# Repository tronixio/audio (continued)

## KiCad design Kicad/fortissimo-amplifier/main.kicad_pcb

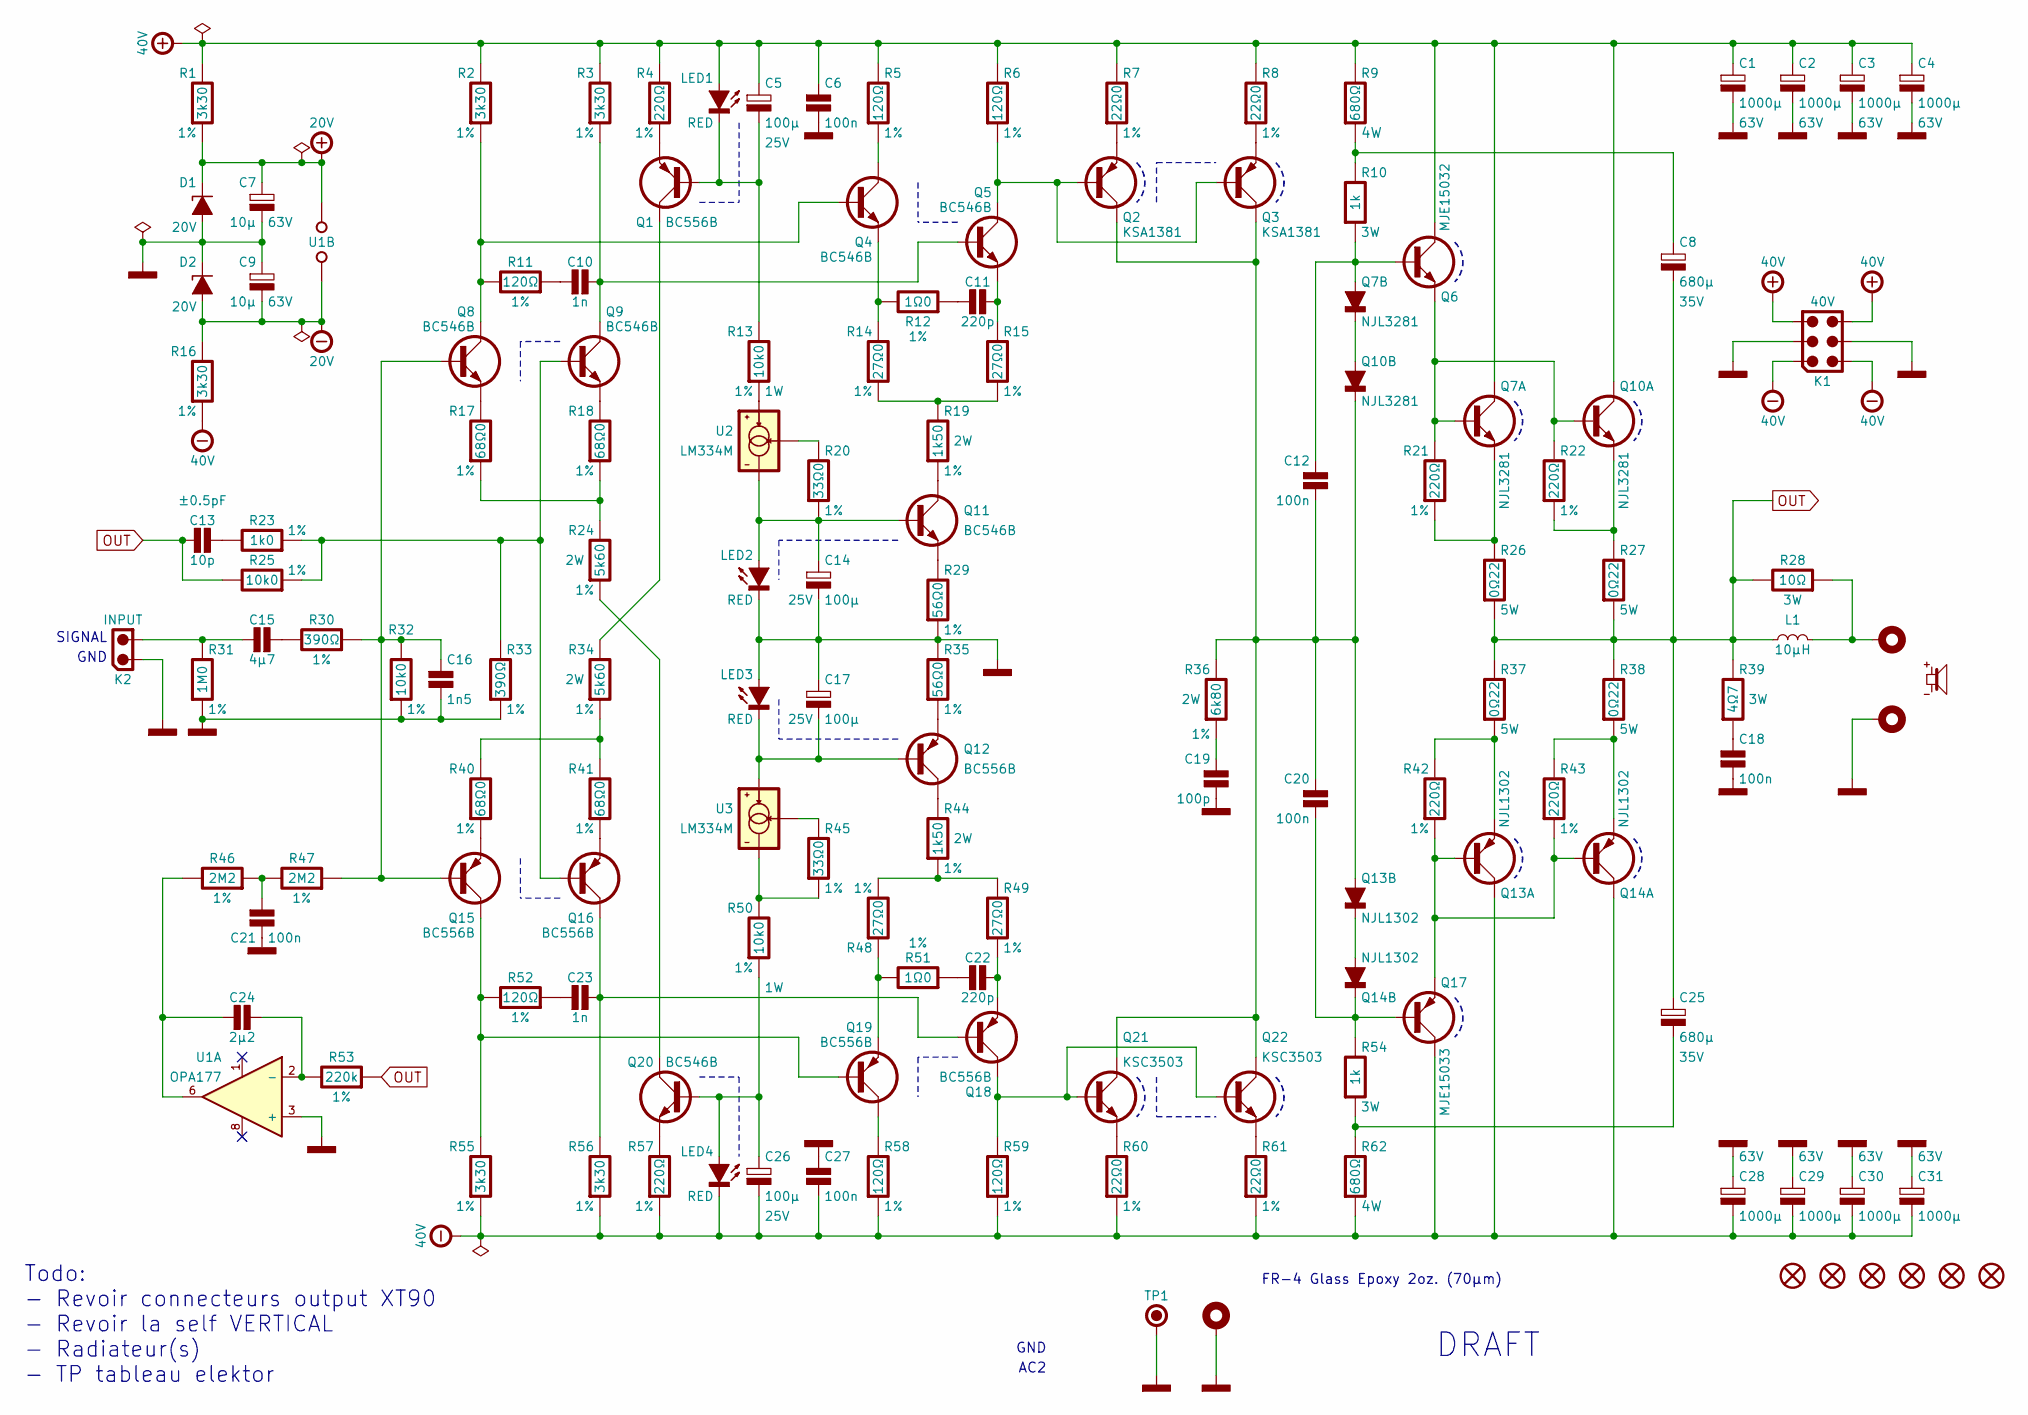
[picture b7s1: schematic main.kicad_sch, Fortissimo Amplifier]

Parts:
C1, C2, C3, C4, C28, C29, C30, C31: 1000µ; CAPACITOR-ELECTROLYTIC-RADIAL-160-350-075-WURTH; Voltage 63V; Tolerance 20%; Mouser 710-860040780017
C5, C14, C17, C26: 100µ; CAPACITOR-ELECTROLYTIC-RADIAL-080-115-035-WURTH; Tolerance 20%; Voltage 25V; Mouser 710-860240474005
C6, C12, C20, C21, C27: 100n; WIMA-FILM-CAPACITOR-RADIAL-100-025-070-075; Tolerance 5%; Voltage 100V; Mouser 505-MKS4D031002AJSSD
C7, C9: 10µ; CAPACITOR-ELECTROLYTIC-RADIAL-050-110-020-WURTH; Voltage 63V; Tolerance 20%; Mouser 710-860020772010
C8, C25: 680µ; CAPACITOR-ELECTROLYTIC-RADIAL-130-200-050-WURTH; Voltage 35V; Tolerance 20%; Mouser 710-860080578019
C10, C23: 1n; WIMA-FILM-CAPACITOR-RADIAL-072-025-065-050; Voltage 63V; Tolerance 5%; Mouser 505-FKS2C01101A0JN0
C11, C22: 220p; WIMA-FILM-CAPACITOR-RADIAL-072-045-060-050; Tolerance 2.5%; Voltage 100V; Mouser 505-FKP2220/100/2.5
C13: 10p; CAPACITOR-SMD-1206; Voltage 100V; Tolerance ±0.5pF; Mouser 581-12061A100DAT2A
C15: 4µ7; WIMA-FILM-CAPACITOR-RADIAL-072-085-140-050; Tolerance 5%; Voltage 63V; Mouser 505-MKS24.7/63/5
C16: 1n5; WIMA-FILM-CAPACITOR-RADIAL-072-025-065-050; Voltage 100V; Tolerance 5%; Mouser 505-FKS2D011501A0JA0
C18: 100n; KEMET-R79-100-050-100-050; Tolerance 5%; Voltage 160V; Mouser 80-R79GC3100Z340J
C19: 100p; WIMA-FILM-CAPACITOR-RADIAL-072-045-060-050; Voltage 100V; Tolerance 2.5%; Mouser 505-FKP2100/100/2.5
C24: 2µ2; WIMA-FILM-CAPACITOR-RADIAL-072-072-130-050; Tolerance 5%; Voltage 63V; Mouser 505-MKS22.2/63/5
D1, D2: 20V; SOD-123; Mouser 771-BZT52-C20
H1, H2, H9: MOUNTING-HOLE-3MM-PAD-VIA
H3, H4, H5, H6, H7, H8: MOUNTING-HOLE-3MM-MASK
K1: 40V; MOLEX-39288060; Mouser 538-39-28-8060
K2: INPUT; MOLEX-532530270; Mouser 538-53253-0270
L1: 10µH; WURTH-744710615
LED1, LED2, LED3, LED4: RED; LED-TH-RECTANGULAR-5MM-2MM; Mouser 630-HLMP-S201
Q1, Q12, Q15, Q16, Q18, Q19: BC556B; TO-92-INLINE-WIDE; Mouser 512-BC556BTF
Q2, Q3: KSA1381; TO-126-3-VERTICAL; Mouser 512-KSA1381ESTU
Q4, Q5, Q8, Q9, Q11, Q20: BC546B; TO-92-INLINE-WIDE; Mouser 512-BC546BTF
Q6: MJE15032; TO-220-3-VERTICAL; Mouser 863-MJE15032G
Q7, Q10: NJL3281; TO-264-5-VERTICAL; Mouser 863-NJL3281DG
Q13, Q14: NJL1302; TO-264-5-VERTICAL; Mouser 863-NJL1302DG
Q17: MJE15033; TO-220-3-VERTICAL; Mouser 863-MJE15033G
Q21, Q22: KSC3503; TO-126-3-VERTICAL; Mouser 512-KSC3503DS
R1, R2, R3, R16, R55, R56: 3k30; RESISTOR-SMD-2512; Tolerance 1%; Mouser 603-RC2512FK-073K3L
R4, R21, R22, R42, R43, R57: 220Ω; RESISTOR-SMD-2512; Tolerance 1%; Mouser 603-RC2512FK-07220RL
R5, R6, R11, R52, R58, R59: 120Ω; RESISTOR-SMD-2512; Tolerance 1%; Mouser 603-RC2512FK-07120RL
R7, R8, R60, R61: 22Ω0; RESISTOR-SMD-2512; Tolerance 1%; Mouser 603-RC2512FK-0722RL
R9, R62: 680Ω; RESISTOR-SMD-2816; Tolerance 5%; Mouser 279-3540680RJT
R10, R54: 1k; RESISTOR-SMD-2512-POWER; Tolerance 5%; Mouser 279-35221K0JT
R12, R51: 1Ω0; RESISTOR-SMD-2512; Tolerance 1%; Mouser 603-RC2512FK-071RL
R13, R25, R32, R50: 10k0; RESISTOR-SMD-2512; Tolerance 1%; Mouser 603-RC2512FK-0710KL
R14, R15, R48, R49: 27Ω0; RESISTOR-SMD-2512; Tolerance 1%; Mouser 603-RC2512FK-0727RL
R17, R18, R40, R41: 68Ω0; RESISTOR-SMD-2512; Tolerance 1%; Mouser 603-RC2512FK-0768RL
R19, R44: 1k50; RESISTOR-SMD-2512-POWER; Tolerance 1%; Mouser 279-CRGP2512F1K5
R20, R45: 33Ω0; RESISTOR-SMD-2512; Tolerance 1%; Mouser 603-RC2512FK-0733RL
R23: 1k0; RESISTOR-SMD-2512; Tolerance 1%; Mouser 603-RC2512FK-071KL
R24, R34: 5k60; RESISTOR-SMD-2512-POWER; Tolerance 1%; Mouser 279-CRGP2512F5K6
R26, R27, R37, R38: 0Ω22; KOA-SPEER-BPR58; Tolerance 5%; Mouser 660-BPR58CR22J
R28: 10Ω; RESISTOR-SMD-2512-POWER; Tolerance 5%; Mouser 279-352210RJT
R29, R35: 56Ω0; RESISTOR-SMD-2512; Tolerance 1%; Mouser 603-RC2512FK-0756RL
R30, R33: 390Ω; RESISTOR-SMD-2512; Tolerance 1%; Mouser 603-RC2512FK-07390RL
R31: 1M0; RESISTOR-SMD-2512; Tolerance 1%; Mouser 603-RC2512FK-071ML
R36: 6k80; RESISTOR-SMD-2512; Tolerance 1%; Mouser 279-CRGP2512F6K8
R39: 4Ω7; RESISTOR-SMD-2512-POWER; Tolerance 5%; Mouser 279-35224R7JT
R46, R47: 2M2; RESISTOR-SMD-2512; Tolerance 1%; Mouser 603-RC2512FK-072M2L
R53: 220k; RESISTOR-SMD-2512; Tolerance 1%; Mouser 603-RC2512FK-07220KL
TP1: KEYSTONE-5006; Mouser 534-5006
U1: OPA177; SOIC-08; Mouser 595-OPA177GS/2K5
U2, U3: LM334M; SOIC-08; Mouser 926-LM334MX/NOPB
X1: (no value)

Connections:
+20V: C7.1, D1.1 (C), R1.2, U1.7 (V+)
+40V: C1.1, C2.1, C3.1, C4.1, C5.1, C6.1, K1.3, K1.6, LED1.2 (A), Q6.2 (C), Q7.3 (C), Q10.3 (C), R1.1, R2.1, R3.1, R4.1, R5.1, R6.1, R7.1, R8.1, R9.1
-20V: C9.2, D2.2 (A), R16.1, U1.4 (V-)
-40V: C26.2, C27.2, C28.2, C29.2, C30.2, C31.2, K1.1, K1.4, LED4.1 (C), Q13.3 (C), Q14.3 (C), Q17.2 (C), R16.2, R55.2, R56.2, R57.2, R58.2, R59.2, R60.2, R61.2, R62.2
GND: C1.2, C2.2, C3.2, C4.2, C6.2, C7.2, C9.1, C14.2, C16.2, C17.1, C18.2, C19.2, C21.2, C27.1, C28.1, C29.1, C30.1, C31.1, D1.2 (A), D2.1 (C), H2.1, H9.1, K1.2, K1.5, K2.1, LED2.1 (C), LED3.2 (A), R29.2, R31.2, R32.2, R33.2, R35.1, TP1.1, U1.3 (+)
unnamed: C8.1, R9.2, R10.1
unnamed: C10.1, R11.2
unnamed: C11.1, R12.2
unnamed: C13.2, R23.1
unnamed: C15.1, K2.2, R31.1
unnamed: C15.2, R30.1
unnamed: C18.1, R39.2
unnamed: C19.1, R36.2
unnamed: C21.1, R46.2, R47.1
unnamed: C22.1, R51.2
unnamed: C23.1, R52.2
unnamed: C24.1, R46.1, U1.6
unnamed: C25.2, R54.2, R62.1
unnamed: H1.1, L1.2, R28.2
unnamed: C5.2, LED1.1 (C), Q1.2 (B), R13.1
unnamed: C14.1, LED2.2 (A), Q11.2 (B), R20.2, U2.2 (V-), U2.3 (V-), U2.6 (V-), U2.7 (V-)
unnamed: C17.2, LED3.1 (C), Q12.2 (B), U3.4 (V+)
unnamed: C26.1, LED4.2 (A), Q20.2 (B), R50.2
unnamed: Q1.1 (C), R34.1
unnamed: Q1.3 (E), R4.2
unnamed: Q2.3 (B), Q3.3 (B), Q5.1 (C), R6.2
unnamed: Q2.1 (E), R7.2
unnamed: Q3.1 (E), R8.2
unnamed: Q4.2 (B), Q8.1 (C), R2.2, R11.1
unnamed: Q4.1 (C), R5.2
unnamed: Q4.3 (E), R12.1, R14.1
unnamed: C10.2, Q5.2 (B), Q9.1 (C), R3.2
unnamed: C11.2, Q5.3 (E), R15.1
unnamed: C12.1, Q6.1 (B), Q7.4 (A), R10.2
unnamed: Q7.2 (E), R21.2, R26.1
unnamed: Q8.3 (E), R17.1
unnamed: Q9.3 (E), R18.1
unnamed: Q6.3 (E), Q7.1 (B), Q10.1 (B), R21.1, R22.1
unnamed: Q10.2 (E), R22.2, R27.1
unnamed: Q7.5 (K), Q10.4 (A)
unnamed: C12.2, C20.1, Q2.2 (C), Q3.2 (C), Q10.5 (K), Q13.4 (A), Q21.2 (C), Q22.2 (C), R36.1
unnamed: Q11.1 (C), R19.2
unnamed: Q11.3 (E), R29.1
unnamed: Q12.1 (C), R44.1
unnamed: Q12.3 (E), R35.2
unnamed: Q13.1 (B), Q14.1 (B), Q17.3 (E), R42.2, R43.2
unnamed: Q13.2 (E), R37.2, R42.1
unnamed: Q13.5 (K), Q14.4 (A)
unnamed: Q14.2 (E), R38.2, R43.1
unnamed: C20.2, Q14.5 (K), Q17.1 (B), R54.1
unnamed: C16.1, Q8.2 (B), Q15.2 (B), R30.2, R32.1, R47.2
unnamed: Q15.1 (C), Q19.2 (B), R52.1, R55.1
unnamed: Q15.3 (E), R40.2
unnamed: Q9.2 (B), Q16.2 (B), R23.2, R25.2, R33.1
unnamed: C23.2, Q16.1 (C), Q18.2 (B), R56.1
unnamed: Q16.3 (E), R41.2
unnamed: Q18.1 (C), Q21.3 (B), Q22.3 (B), R59.1
unnamed: C22.2, Q18.3 (E), R49.2
unnamed: Q19.1 (C), R58.1
unnamed: Q19.3 (E), R48.2, R51.1
unnamed: Q20.1 (C), R24.2
unnamed: Q20.3 (E), R57.1
unnamed: Q21.1 (E), R60.1
unnamed: Q22.1 (E), R61.1
unnamed: R14.2, R15.2, R19.1
unnamed: R17.2, R18.2, R24.1
unnamed: R34.2, R40.1, R41.1
unnamed: R44.2, R48.1, R49.1
unnamed: R45.2, R50.1, U3.2 (V-), U3.3 (V-), U3.6 (V-), U3.7 (V-)
unnamed: C24.2, R53.1, U1.2 (-)
unnamed: R20.1, U2.1 (R)
unnamed: R13.2, U2.4 (V+)
unnamed: R45.1, U3.1 (R)
OUT: C8.2, C13.1, C25.1, L1.1, R25.1, R26.2, R27.2, R28.1, R37.1, R38.1, R39.1, R53.2

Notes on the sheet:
FR-4 Glass Epoxy 2oz. (70µm)
GND
DRAFT
SIGNAL
AC2
Todo: - Revoir connecteurs output XT90 - Revoir la self VERTICAL - Radiateur(s) - TP tableau elektor

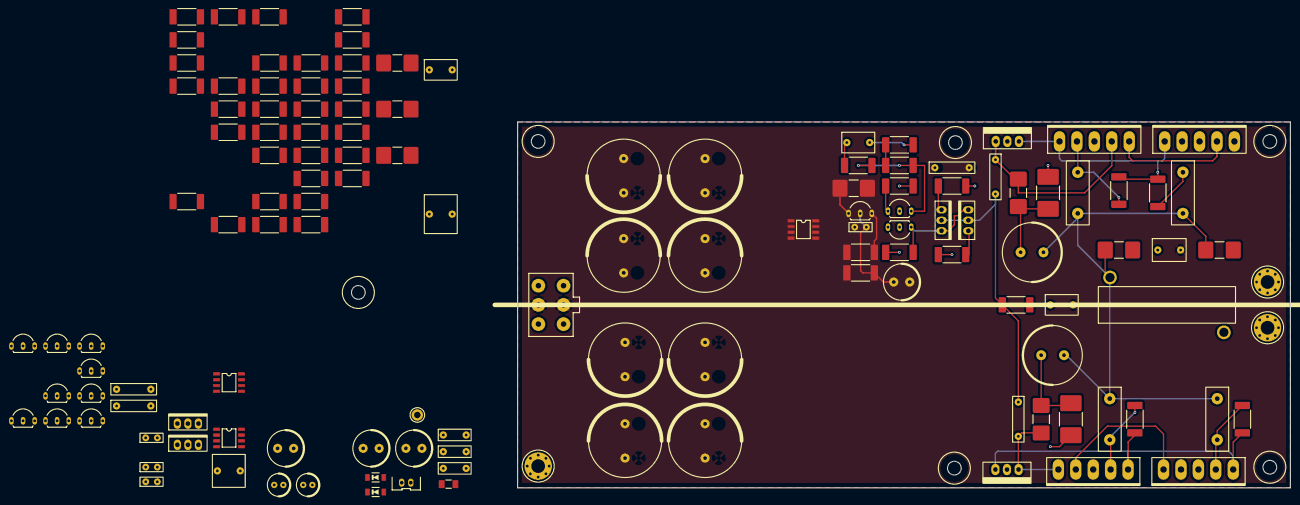
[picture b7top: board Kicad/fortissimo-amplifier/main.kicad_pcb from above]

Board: 4 copper layers, 169.0 x 80.0 mm, 138 parts (0 on the bottom side), 74 nets.

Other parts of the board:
kibuzzard-65E2F8E3: G***; kibuzzard-65E2F8E3

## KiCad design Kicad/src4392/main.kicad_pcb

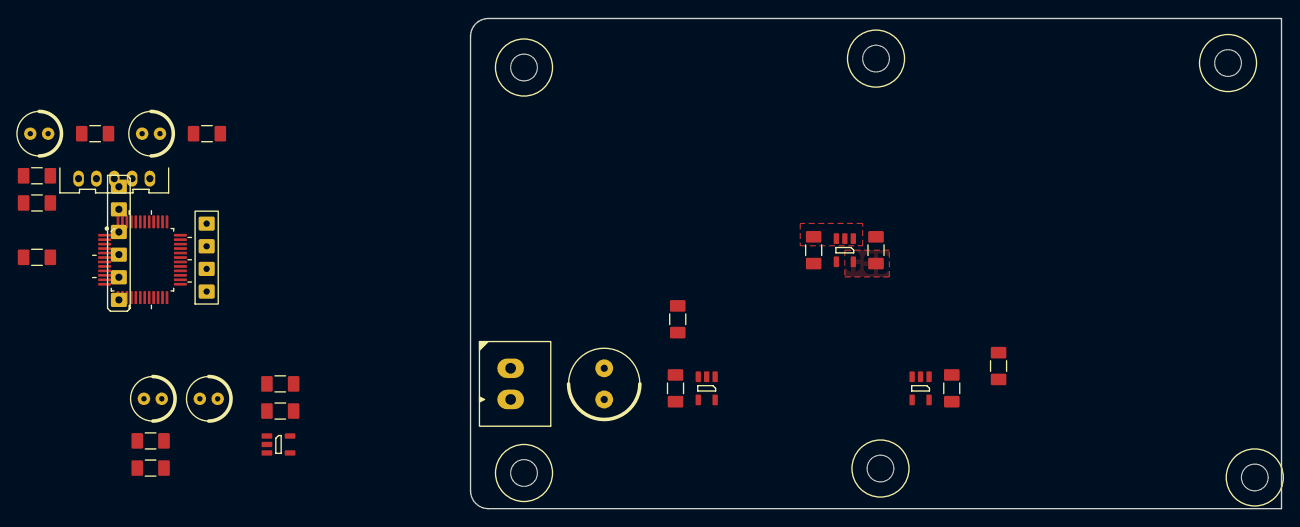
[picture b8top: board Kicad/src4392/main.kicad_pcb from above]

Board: 2 copper layers, 91.0 x 55.0 mm, 37 parts (0 on the bottom side), 8 nets, no tracks yet.

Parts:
C101: 47µ; CAPACITOR-ELECTROLYTIC-RADIAL-080-115-035-WURTH
C102, C103, C104, C105, C106, C107, C108, C109: 1µ; CAPACITOR-SMD-1206
C201, C204, C208, C210: 10µ; CAPACITOR-ELECTROLYTIC-RADIAL-050-110-020-WURTH
C202, C206: 2µ2; CAPACITOR-SMD-1206
C203, C205, C207, C209: 100n; CAPACITOR-SMD-1206
H101, H102, H103, H104, H105, H106: MOUNTING-HOLE-3MM-MASK
K101: VCC; MOLEX-532580229
K201: CLOCK; HARWIN-M20-782044x
K202: MCU; HARWIN-M20-999064x
K203: I2S OUTPUT; MOLEX-532530570
R201: 10K; RESISTOR-SMD-1206
U101: AP7375-18; SOT25
U102, U103, U104: AP7375-33; SOT25
U201: SRC4392; TQFP-48
kibuzzard-63CAF235: G***; kibuzzard-63CAF235
kibuzzard-63CBA350: G***; kibuzzard-63CBA350

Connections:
+1V8D: C103.1, C201.1, C203.1, U101.5 (VOUT), U201.17 (VDD18_(DCORE))
+3V3A: C109.1, U104.5 (VOUT)
+3V3D: C105.1, C204.1, C205.1, U102.5 (VOUT), U201.33 (VDD33_(DIR/DIT))
+3V3L: C107.1, C209.1, C210.1, U103.5 (VOUT), U201.42 (VIO_(LOGIC))
AGND: C101.2, C102.2, C103.2, C104.2, C105.2, C106.2, C107.2, C108.2, C109.2, C202.2, K101.1, K201.4, K202.6, R201.2, U101.2 (GND), U102.2 (GND), U103.2 (GND), U104.2 (GND), U201.16 (DGND1_(DCORE)), U201.30 (DGND2_(DIR/DIT))
unnamed: U201.19 (A0), U201.21 (A1), U201.43 (DGND3_(LOGIC))
unnamed: C207.1, C208.1, U201.9 (VCC)
VCC: C101.1, C102.1, C104.1, C106.1, C108.1, K101.2, U101.1 (VIN), U101.3 (EN), U102.1 (VIN), U102.3 (EN), U103.1 (VIN), U103.3 (EN), U104.1 (VIN), U104.3 (EN)

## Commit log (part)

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2023-01-28 ES9023
2023-02-18 Preamp A/D
2023-02-23 chore
2023-03-01 Add PCM179x
2026-04-26 PSS 25VA
2026-04-26 PSUD
2026-04-28 PSRD LM2596-50
